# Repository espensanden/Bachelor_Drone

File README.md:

# Bachelor_Drone
This is our bachelorsproject of the use of Drones in an off-shore environment.

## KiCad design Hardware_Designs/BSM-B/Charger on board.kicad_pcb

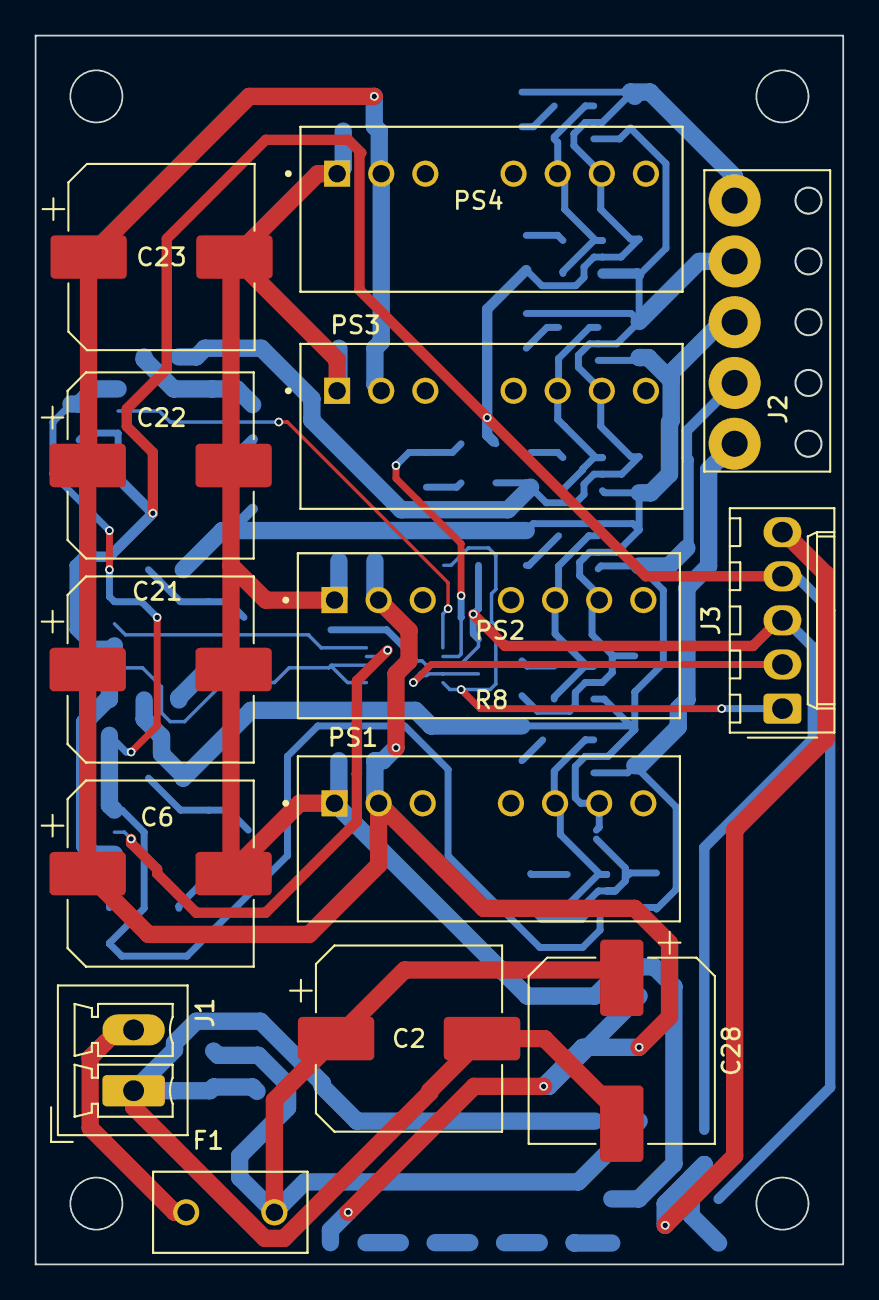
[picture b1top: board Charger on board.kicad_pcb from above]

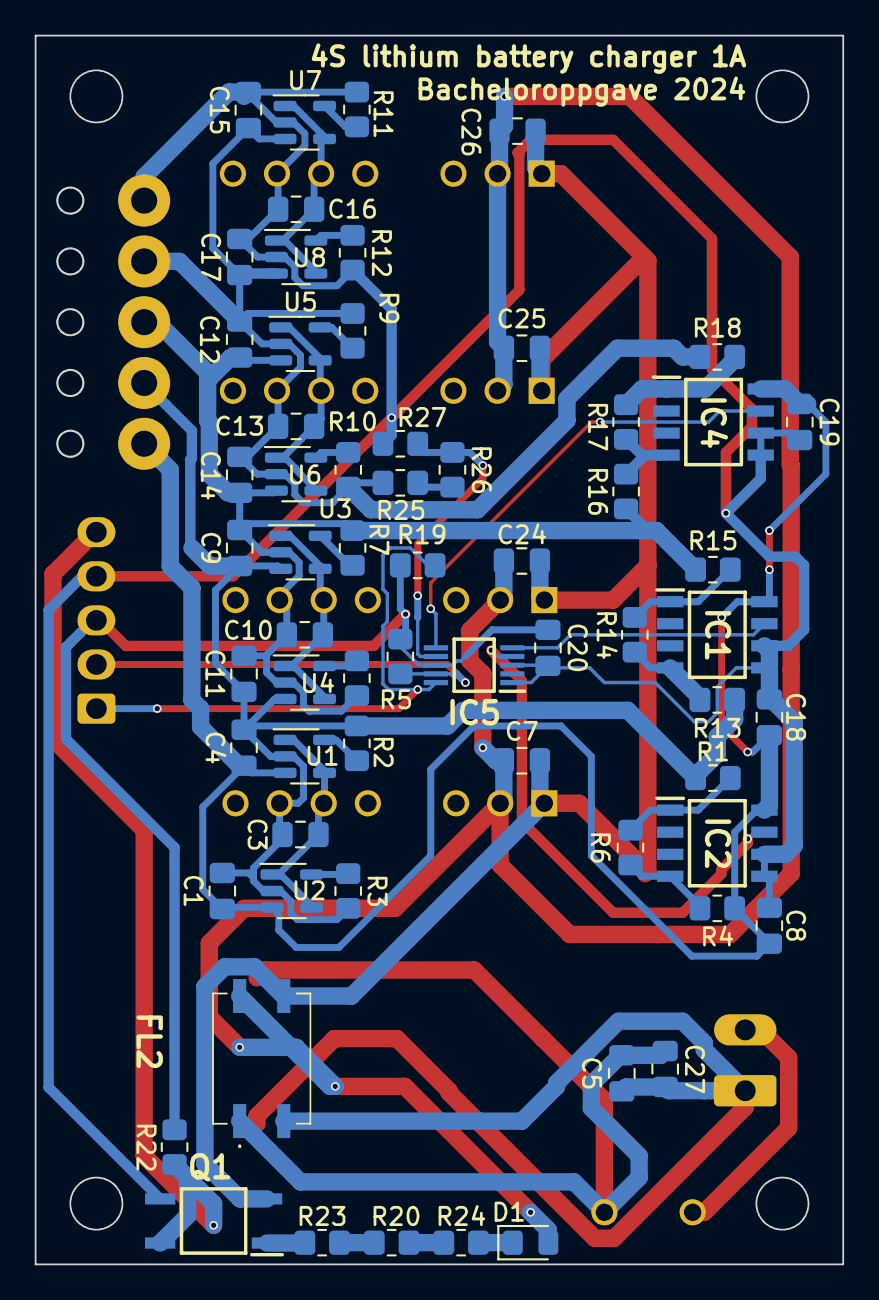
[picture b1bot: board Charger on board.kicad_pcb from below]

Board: 2 copper layers, 46.5 x 70.7 mm, 77 parts (63 on the bottom side), 41 nets.

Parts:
C1, C4, C9, C11, C12, C14, C15, C17: 1uC; C_0805_2012Metric_Pad1.18x1.45mm_HandSolder
C2, C6, C21, C22, C23, C28: 330uFE; CP_Elec_10x14.3
C3, C10, C13, C16: 22uC; C_0805_2012Metric_Pad1.18x1.45mm_HandSolder
C5, C7, C24, C25, C26, C27: 10uC; C_0805_2012Metric_Pad1.18x1.45mm_HandSolder
C8, C18, C19, C20: 100nC; C_0805_2012Metric_Pad1.18x1.45mm_HandSolder
D1: LED; LED_0805_2012Metric_Pad1.15x1.40mm_HandSolder
F1: Fuse; FUSE_BK_PCE-5-R
FL2: DFT7160-475BLC; DFT7160475BLC
IC1, IC2, IC4: INA826AID; SOIC127P600X175-8N
IC5: ADS1015IDGST; SOP50P490X110-10N
J1: Conn_01x02; PhoenixContact_MCV_1,5_2-G-3.5_1x02_P3.50mm_Vertical
J2: Batteri plug; wire hole 6mm 5stk
J3: PI5; Molex_KK-254_AE-6410-05A_1x05_P2.54mm_Vertical
PS1, PS2, PS3, PS4: URB2405S-6WR3; CONV_URB2405S-6WR3
Q1: HCPL-181-00DE; SOP254P675X240-4N
R1, R15, R18, R26: 1kR; R_0805_2012Metric_Pad1.20x1.40mm_HandSolder
R2, R3, R7, R8, R9, R10, R11, R12, R20, R23, R24: 2kR; R_0805_2012Metric_Pad1.20x1.40mm_HandSolder
R4, R13, R16: 39kR; R_0805_2012Metric_Pad1.20x1.40mm_HandSolder
R5, R6, R14, R17, R19: 10kR; R_0805_2012Metric_Pad1.20x1.40mm_HandSolder
R22: 100kR; R_0805_2012Metric_Pad1.20x1.40mm_HandSolder
R25: R39k; R_0805_2012Metric_Pad1.20x1.40mm_HandSolder
R27: R10k; R_0805_2012Metric_Pad1.20x1.40mm_HandSolder
U1, U2, U3, U4, U5, U6, U7, U8: MCP73812T-420I-OT; SOT-23-5

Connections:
+24V: F1.1, J1.2
GND: C8.2, C15.2, C16.2, C17.2, C18.2, C19.2, C20.2, IC1.5 (-VS), IC1.6 (REF), IC2.5 (-VS), IC2.6 (REF), IC4.5 (-VS), IC4.6 (REF), IC5.1 (ADDR), IC5.3 (GND), J2.5, J3.4, PS4.7 (0V), Q1.3 (EMITTER), R11.2, R12.2, R27.2, U7.2 (V_{SS}), U8.2 (V_{SS})
GND2: C2.2, C5.2, C27.2, C28.2, FL2.2, J1.1
unnamed: C2.1, C5.1, C27.1, C28.1, F1.2, FL2.1
unnamed: C6.1, C7.1, C21.1, C22.1, C23.1, C24.1, C25.1, C26.1, D1.2 (A), FL2.4, PS1.2 (VIN), PS2.2 (VIN), PS3.2 (VIN), PS4.2 (VIN)
unnamed: D1.1 (K), R24.1
unnamed: IC1.4 (+IN), R13.2, R14.1
unnamed: C1.1, C4.1, C8.1, C18.1, C19.1, IC1.8 (+VS), IC2.8 (+VS), IC4.8 (+VS), J2.1, R4.1, U1.3 (V_{BAT}), U2.3 (V_{BAT})
unnamed: IC1.1 (-IN), R14.2, R15.2
unnamed: IC1.7 (VOUT), IC5.5 (AIN1)
unnamed: IC2.4 (+IN), R4.2, R6.1
unnamed: IC2.1 (-IN), R1.2, R6.2
unnamed: IC2.7 (VOUT), IC5.4 (AIN0)
unnamed: IC4.4 (+IN), R16.2, R17.1
unnamed: IC4.1 (-IN), R17.2, R18.2
unnamed: IC4.7 (VOUT), IC5.6 (AIN2)
unnamed: IC5.7 (AIN3), R26.1, R27.1
unnamed: IC5.10 (SCL), J3.1, R19.2
unnamed: IC5.9 (SDA), J3.2, R5.2
unnamed: C20.1, IC5.8 (VDD), J3.3, R5.1, R19.1, R22.2
unnamed: C1.2, C3.2, C4.2, C9.1, C11.1, J2.2, PS1.7 (0V), R1.1, R2.2, R3.2, R13.1, U1.2 (V_{SS}), U2.2 (V_{SS}), U3.3 (V_{BAT}), U4.3 (V_{BAT})
unnamed: C9.2, C10.2, C11.2, C12.1, C14.1, J2.3, PS2.7 (0V), R7.2, R8.2, R15.1, R16.1, U3.2 (V_{SS}), U4.2 (V_{SS}), U5.3 (V_{BAT}), U6.3 (V_{BAT})
unnamed: C12.2, C13.2, C14.2, C15.1, C17.1, J2.4, PS3.7 (0V), R9.2, R10.2, R18.1, R25.1, U5.2 (V_{SS}), U6.2 (V_{SS}), U7.3 (V_{BAT}), U8.3 (V_{BAT})
unnamed: J3.5, Q1.4 (COLLECTOR), R22.1
unnamed: C3.1, PS1.6 (+VO), U1.1 (CE), U1.4 (V_{DD}), U2.1 (CE), U2.4 (V_{DD})
unnamed: C6.2, C7.2, C21.2, C22.2, C23.2, C24.2, C25.2, C26.2, FL2.3, PS1.1 (GND), PS2.1 (GND), PS3.1 (GND), PS4.1 (GND), Q1.2 (CATHODE)
unnamed: C10.1, PS2.6 (+VO), U3.1 (CE), U3.4 (V_{DD}), U4.1 (CE), U4.4 (V_{DD})
unnamed: C13.1, PS3.6 (+VO), U5.1 (CE), U5.4 (V_{DD}), U6.1 (CE), U6.4 (V_{DD})
unnamed: C16.1, PS4.6 (+VO), U7.1 (CE), U7.4 (V_{DD}), U8.1 (CE), U8.4 (V_{DD})
unnamed: Q1.1 (ANODE), R23.2
unnamed: R20.1, R24.2
unnamed: R20.2, R23.1
unnamed: R25.2, R26.2
unnamed: R2.1, U1.5 (PROG)
unnamed: R3.1, U2.5 (PROG)
unnamed: R7.1, U3.5 (PROG)
unnamed: R8.1, U4.5 (PROG)
unnamed: R9.1, U5.5 (PROG)
unnamed: R10.1, U6.5 (PROG)
unnamed: R11.1, U7.5 (PROG)
unnamed: R12.1, U8.5 (PROG)

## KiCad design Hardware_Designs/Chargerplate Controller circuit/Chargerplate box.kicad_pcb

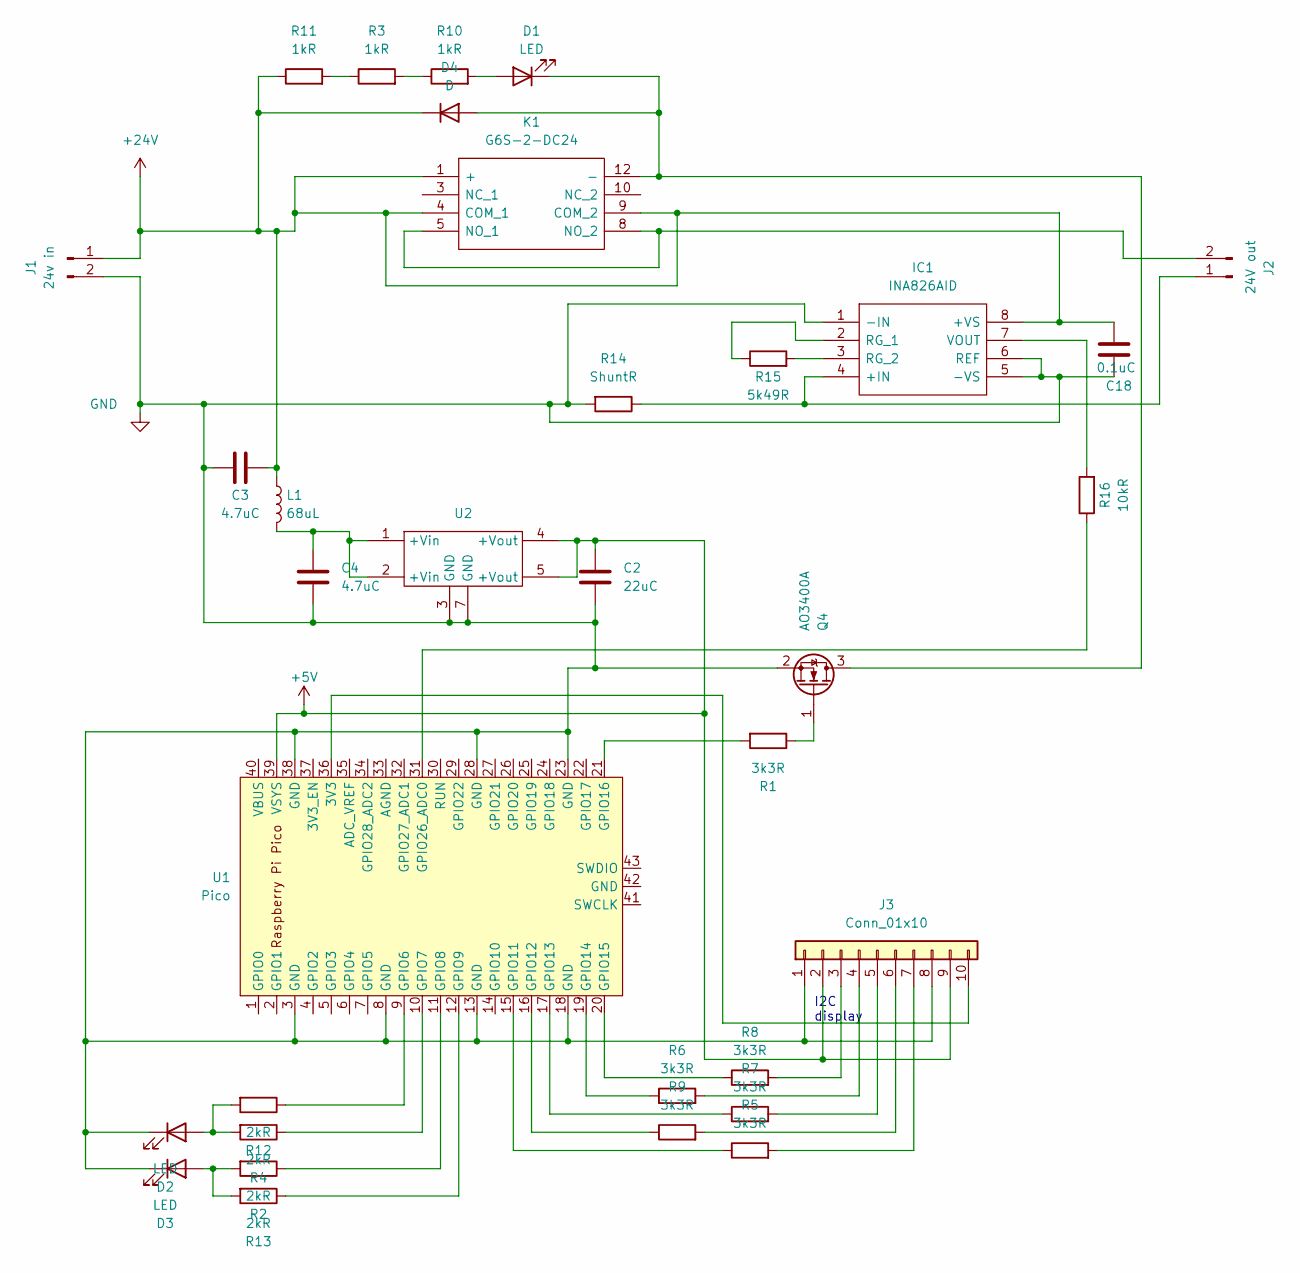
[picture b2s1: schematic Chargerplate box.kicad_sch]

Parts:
C2: 22uC; C_0805_2012Metric_Pad1.18x1.45mm_HandSolder
C3, C4: 4.7uC; C_0805_2012Metric_Pad1.18x1.45mm_HandSolder
C18: 0.1uC; C_0805_2012Metric_Pad1.18x1.45mm_HandSolder
D1, D2, D3: LED; LED_D5.0mm
D4: D; D_0805_2012Metric_Pad1.15x1.40mm_HandSolder
IC1: INA826AID; SOIC127P600X175-8N; Manufacturer_Part_Number INA826AID; Mouser Part Number 595-INA826AID
J1: 24v in; PhoenixContact_MCV_1,5_2-G-3.5_1x02_P3.50mm_Vertical
J2: 24V out; PhoenixContact_MCV_1,5_2-G-3.5_1x02_P3.50mm_Vertical
J3: Conn_01x10; PinSocket_1x10_P2.54mm_Vertical
K1: G6S-2-DC24; G6S2DC12; Manufacturer_Part_Number G6S-2-DC24; Mouser Part Number 653-G6S-2-DC24
L1: 68uL; C_2220_5650Metric_Pad1.97x5.40mm_HandSolder
Q4: AO3400A; SOT-23_Handsoldering; LCSC C20917
R1, R5, R6, R7, R8, R9: 3k3R; R_0805_2012Metric_Pad1.20x1.40mm_HandSolder
R2, R4, R12, R13: 2kR; R_0805_2012Metric_Pad1.20x1.40mm_HandSolder
R3, R10, R11: 1kR; R_0805_2012Metric_Pad1.20x1.40mm_HandSolder
R14: ShuntR; R_1206_3216Metric_Pad1.30x1.75mm_HandSolder
R15: 5k49R; R_0805_2012Metric_Pad1.20x1.40mm_HandSolder
R16: 10kR; R_0805_2012Metric_Pad1.20x1.40mm_HandSolder
U1: Pico; Pico_pin_THT
U2: SVR10S05

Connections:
+5V: C2.2, J3.2, J3.9, U1.39 (VSYS), U2.4 (+Vout), U2.5 (+Vout)
+24V: C3.1, D4.1 (K), IC1.8 (+VS), J1.1, K1.1 (+), K1.4 (COM_1), K1.9 (COM_2), L1.1, R11.1; also elsewhere on the board
GND: C2.1, C3.2, C4.2, D2.1 (K), D3.1 (K), IC1.1 (-IN), IC1.5 (-VS), IC1.6 (REF), J1.2, J3.1, J3.8, R14.2, U1.3 (GND), U1.8 (GND), U1.13 (GND), U1.18 (GND), U1.23 (GND), U1.28 (GND), U1.38 (GND), U2.3 (GND), U2.7 (GND); also elsewhere on the board
unnamed: C4.1, L1.2, U2.1 (+Vin), U2.2 (+Vin)
unnamed: D1.2 (A), R10.2
unnamed 5: D1.1 (K), D4.2 (A), K1.12 (-); also elsewhere on the board
unnamed: D2.2 (A), R4.2, R12.2
unnamed: D3.2 (A), R2.2, R13.2
unnamed: IC1.4 (+IN), J2.1, R14.1
unnamed: IC1.2 (RG_1), R15.1
unnamed: IC1.3 (RG_2), R15.2
unnamed: IC1.7 (VOUT), R16.2
unnamed: J2.2, K1.5 (NO_1), K1.8 (NO_2)
unnamed: J3.3, R8.2
unnamed: J3.4, R6.2
unnamed: J3.5, R7.2
unnamed: J3.6, R9.2
unnamed: J3.7, R5.2
unnamed: J3.10, U1.36 (3V3)
unnamed 19: R1.1; also elsewhere on the board
unnamed: R3.2, R10.1
unnamed: R3.1, R11.2
unnamed: R12.1, U1.9 (GPIO6)
unnamed: R4.1, U1.10 (GPIO7)
unnamed: R2.1, U1.11 (GPIO8)
unnamed: R13.1, U1.12 (GPIO9)
unnamed: R5.1, U1.15 (GPIO11)
unnamed: R9.1, U1.16 (GPIO12)
unnamed: R7.1, U1.17 (GPIO13)
unnamed: R6.1, U1.19 (GPIO14)
unnamed: R8.1, U1.20 (GPIO15)
unnamed: R1.2, U1.21 (GPIO16)
unnamed 32: R16.1, U1.31 (GPIO26_ADC0); also elsewhere on the board

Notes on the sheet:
I2C display

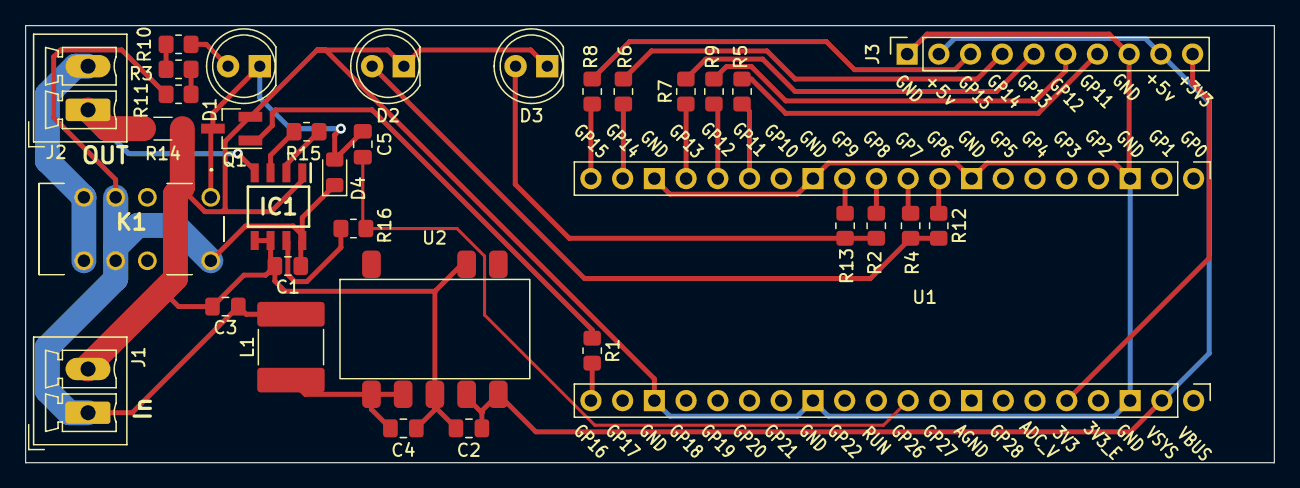
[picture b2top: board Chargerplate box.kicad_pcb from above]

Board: 2 copper layers, 100.0 x 35.0 mm, 34 parts (0 on the bottom side), 33 nets.

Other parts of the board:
C1, C5: 0.1uC; C_0805_2012Metric_Pad1.18x1.45mm_HandSolder
Q1: AO3400A; SOT-23_Handsoldering

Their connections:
+24V: C1.1; also elsewhere on the board
GND: C1.2, Q1.2 (S); also elsewhere on the board
unnamed 5: C5.2, Q1.3 (D); also elsewhere on the board
unnamed 19: Q1.1 (G); also elsewhere on the board
unnamed 32: C5.1; also elsewhere on the board

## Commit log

2024-02-22 Lagt til et script
2024-04-08 Oppretta aruco script
2024-04-08 fixed pose_estimation
2024-04-08 move while true
2024-04-08 new test script for pose
2024-04-08 Some small changes
2024-04-08 small change
2024-04-08 Put in some counts and fps counter
2024-04-08 fps counter
2024-04-08 some changes
2024-04-09 aruco tester
2024-04-09 aruco tester fixed
2024-04-09 changed webcamvideostream
2024-04-09 some stuff
2024-04-09 facedetection
2024-04-09 change
2024-04-09 Fixed variable
2024-04-09 changed im to frame_np
2024-04-09 commented out something
2024-04-09 added new x11_cam
2024-04-09 new backend conf
2024-04-09 changed some stuff
2024-04-09 lala
2024-04-09 changed resolution
2024-04-09 ny algoritme
2024-04-09 Changed a lot of stuff
2024-04-09 changed stuff
2024-04-09 added function
2024-04-09 changed to frame
2024-04-09 changed back to im
2024-04-09 jaja
2024-04-09 changed im
2024-04-09 adad
2024-04-09 false
2024-04-09 changed name
2024-04-09 removed frame
2024-04-09 deleted some files
2024-04-09 dada
2024-04-09 changed something
2024-04-09 adada
2024-04-09 moved while loop
2024-04-09 fafa
2024-04-09 dfssf
2024-04-09 daddada
2024-04-09 sadad
2024-04-09 daaafa
2024-04-09 fafsae
2024-04-09 fafefesffe
2024-04-09 fesfssf
2024-04-09 fesfs
2024-04-09 fsfsgs
2024-04-09 fsefse
2024-04-10 changes something
2024-04-10 Made new file
2024-04-10 fsfe
2024-04-11 added arm_test
2024-04-11 changed
2024-04-11 Create delete_me
2024-04-11 Create deleteme
2024-04-11 Takeoff and land
2024-04-12 changed to 1.5m height
2024-04-12 Added a sleep command
2024-04-12 entered some print statements
2024-04-12 Changed target alltitude to 1m
2024-04-17 Added presicion land done script
2024-04-17 Added ManualArm variable
2024-04-18 changed height to 2m
2024-04-18 hhhh
2024-04-18 gbgvg
2024-04-18 new takeoff
2024-04-18 bhbhbh
2024-04-18 dafeafafa
2024-04-18 bhub
2024-04-18 vukb
2024-04-18 femfes
2024-04-18 gvukuj
2024-04-19 ADS read
2024-04-19 ADS to try
2024-04-19 alog in while loop
2024-04-19 analog_voltage
2024-04-19 server_thread
2024-04-19 remove extra server
2024-04-19 send message to pc
2024-04-19 server = run_server()
2024-04-19 print hi
2024-04-19 comment if time.time() % 10 == 0:
2024-04-19 remove thread comment
2024-04-19 elif message == 'BATTERY_STATS'
2024-04-19 rasbat
2024-04-19 remove thread
2024-04-19 change place
2024-04-19 "BATTERY_STATS"
2024-04-19 change console to sendcommandras
2024-04-19 for key, i in analog_voltage.items():
2024-04-19 _all
2024-04-19 update cell1 voltage
2024-04-19 add :
2024-04-19 all ads_to_voltage1
2024-04-19 battery percent
2024-04-24 camera in station
2024-04-25 Added flight script
2024-04-25 camera ip
2024-04-25 frsg
2024-04-25 afjafe
2024-04-25 cdcsfs
2024-04-25 fafafea
2024-04-26 dhjfkfkd
2024-04-26 hdjfk
2024-04-26 shsjdkd
2024-04-26 ip update
2024-04-26 hbuyvubo
2024-04-26 bijijk
2024-04-26 fhfekfe
2024-04-26 bijnij
2024-04-26 yubibi
2024-04-26 feanjelfea
2024-04-26 fefjoaef
2024-04-27 finseofesno
2024-04-27 fefsfse
2024-04-27 endret fart
2024-04-27 hbkjnkj
2024-04-30 added battery status script
2024-04-30 Remove batery eq and for
2024-04-30 remove line
2024-05-08 Ras voltage read for
2024-05-08 js print
2024-05-08 number batery
2024-05-08 console.log(BATTERY_VOLTAGE_CELL1) = number(BATTERY_VOLTAGE_CELL1);
2024-05-08 parseInt
2024-05-08 remove +10
2024-05-08 Changed flight_101
2024-05-08 typeof
2024-05-08 parseFloat
2024-05-11 gps cord
2024-05-11 test push
2024-05-11 target c
2024-05-12 Coment cv2.imshow
2024-05-12 add print and height 3
2024-05-12 targetAltitude=3
2024-05-12 Endret takeoff og target altitude til 2.
2024-05-12 Endret tilbake til 3
2024-05-12 Endret til 3.2
2024-05-12 Endret til 2 meter
2024-05-14 changed altitude
2024-05-14 change color on indicator light
2024-05-14 changed to two meters
2024-05-14 fligth waypoint 1
2024-05-14 wp home land
2024-05-14 changed height
2024-05-14 added new things to send land message
2024-05-14 math
2024-05-21 new waypoint
2024-05-21 Fjernet z
2024-05-21 same waypoint
2024-05-23 Clean GCS clean up
2024-05-23 Create Other_files
2024-05-23 Create hardware
2024-05-23 clean up
2024-06-03 added waypoints
2024-06-03 added new wp
2024-06-03 kjør
